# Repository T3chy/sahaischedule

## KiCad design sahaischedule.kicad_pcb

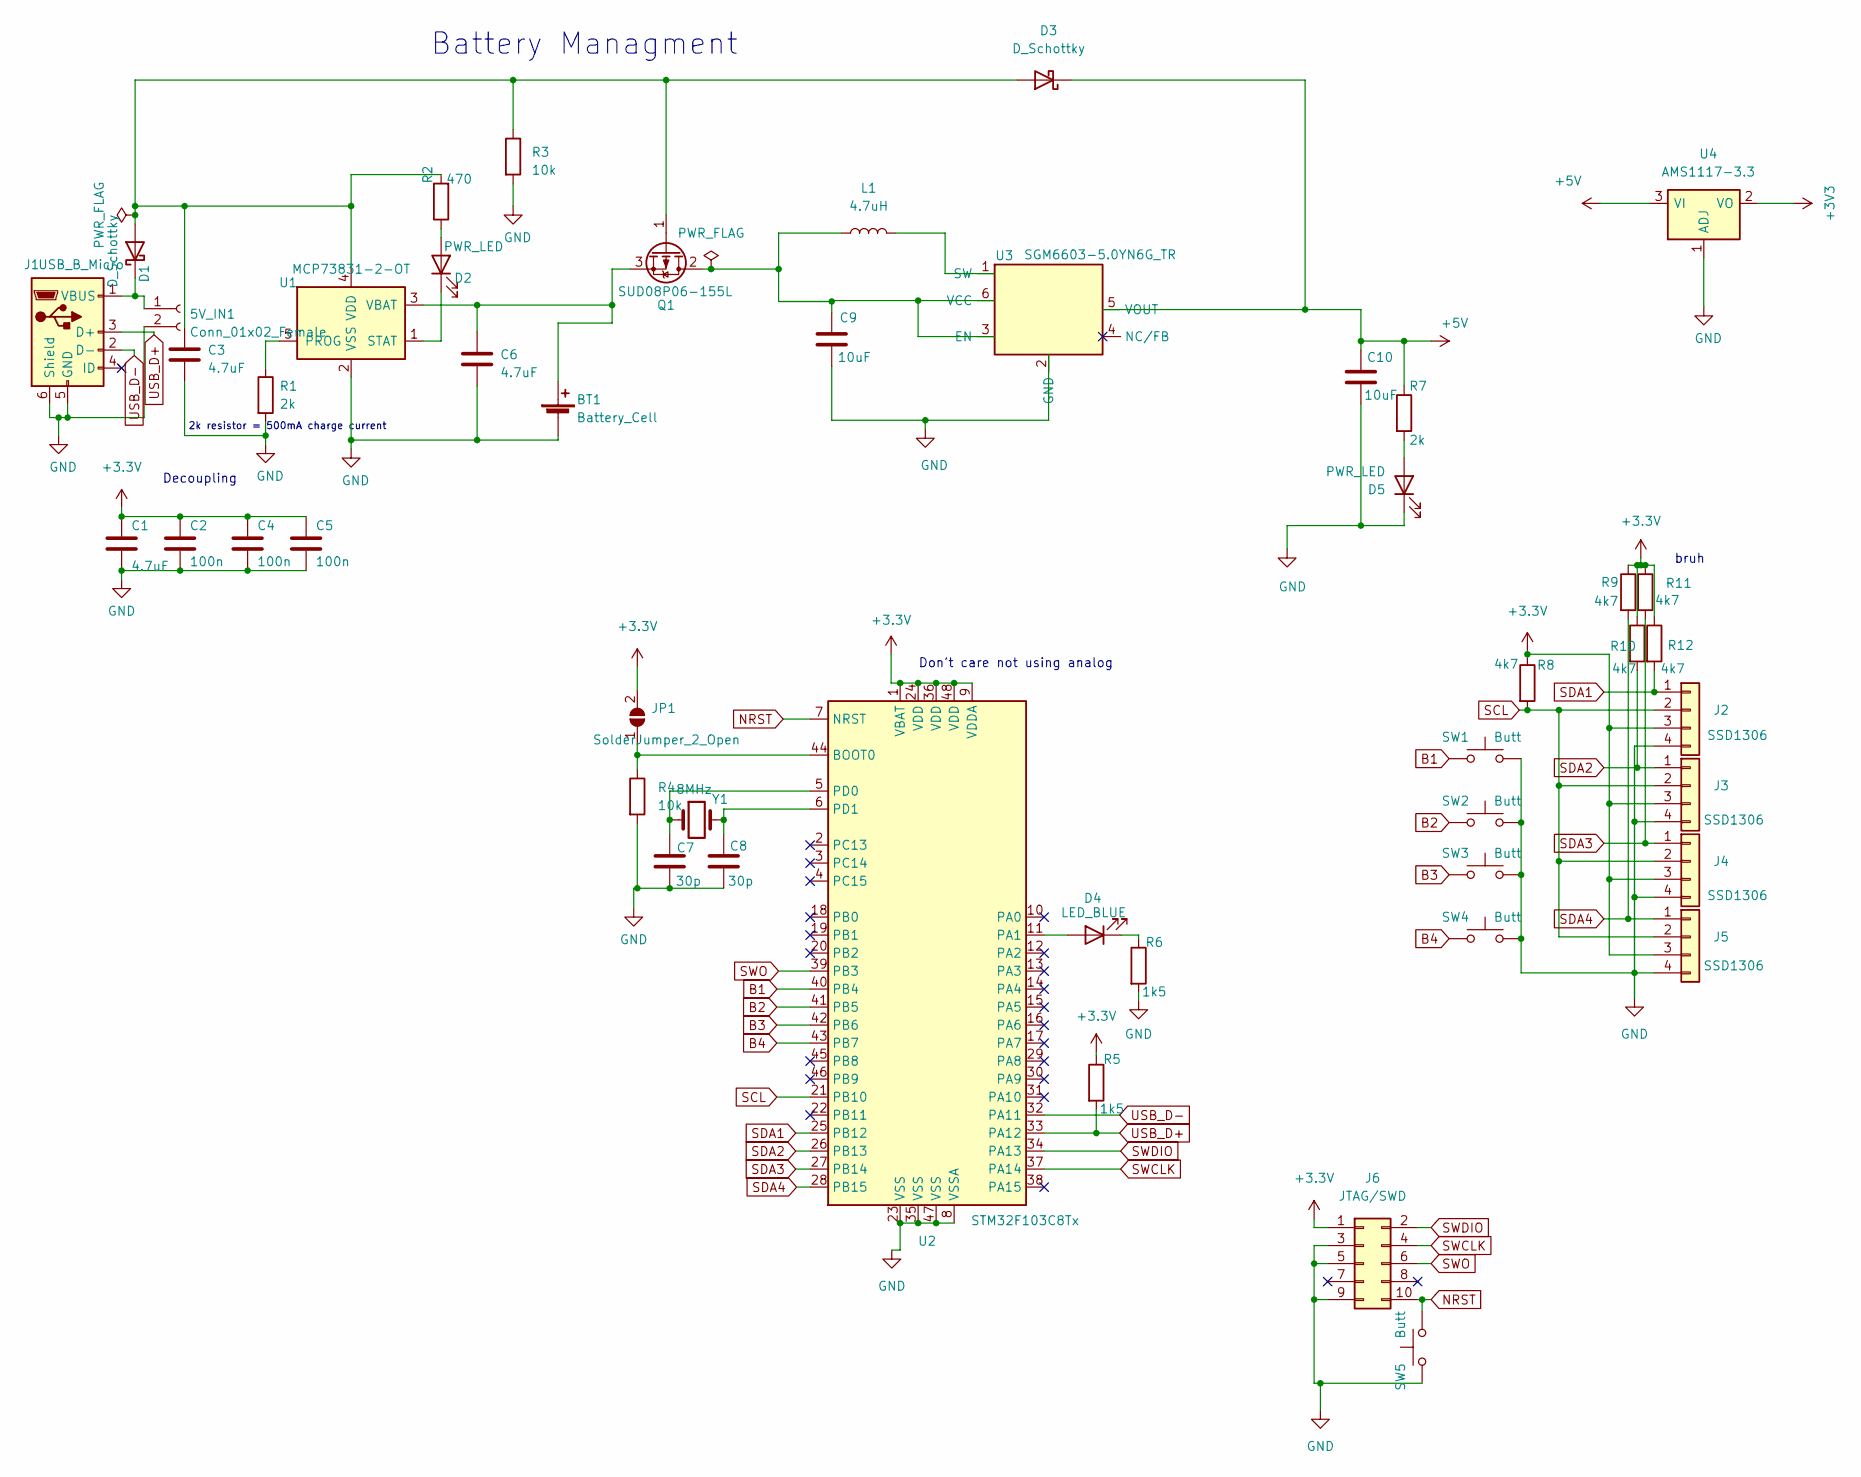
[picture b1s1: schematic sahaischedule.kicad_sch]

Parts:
5V_IN1: Conn_01x02_Female; PinHeader_1x02_P2.54mm_Vertical; mfr_part_num C124375; LCSC C124375
BT1: Battery_Cell; JST_EH_S2B-EH_1x02_P2.50mm_Horizontal; mfr_part_num A2501WR-2P; LCSC C225399
C1, C3, C6: 4.7uF; C_0805_2012Metric_Pad1.18x1.45mm_HandSolder; LCSC C408144
C2, C4, C5: 100n; C_0805_2012Metric_Pad1.18x1.45mm_HandSolder; LCSC C495959
C7, C8: 30p; C_0805_2012Metric_Pad1.18x1.45mm_HandSolder
C9, C10: 10uF; C_0805_2012Metric_Pad1.18x1.45mm_HandSolder
D1, D3: D_Schottky; D_SOD-123; LCSC C8598
D2, D5: PWR_LED; LED_0805_2012Metric; LCSC C72037
D4: LED_BLUE; LED_0805_2012Metric
J1: USB_B_Micro; USB_Micro-B_Molex-105017-0001; mfr_part_num MicroXNJ; LCSC C404969
J2, J3, J4, J5: SSD1306; ssd1306_128x32_breakout
J6: JTAG/SWD; PinHeader_2x05_P1.27mm_Vertical_SMD
JP1: SolderJumper_2_Open; SolderJumper-2_P1.3mm_Open_Pad1.0x1.5mm
L1: 4.7uH; C_0805_2012Metric; LCSC C479902
Q1: SUD08P06-155L; TO-252-2; LCSC C558294
R1, R7: 2k; R_0805_2012Metric_Pad1.20x1.40mm_HandSolder; LCSC C328391
R2: 470; R_0805_2012Metric_Pad1.20x1.40mm_HandSolder; LCSC C136570
R3, R4: 10k; R_0805_2012Metric_Pad1.20x1.40mm_HandSolder
R5, R6: 1k5; R_0805_2012Metric_Pad1.20x1.40mm_HandSolder
R8, R9, R10, R11, R12: 4k7; R_0805_2012Metric_Pad1.20x1.40mm_HandSolder
SW1, SW2, SW3, SW4, SW5: Butt; SW_SPST_Omron_B3FS-101xP; LCSC C589246
U1: MCP73831-2-OT; SOT-23-5; LCSC C424093
U2: STM32F103C8Tx; LQFP-48_7x7mm_P0.5mm; Mouser 497-18592-ND
U3: SGM6603-5.0YN6G_TR; SOT-23-6; LCSC C79689
U4: AMS1117-3.3; SOT-223-3_TabPin2; mfr_part_num AMS1117-3.3; LCSC C369933
Y1: 8MHz; Crystal_SMD_5032-2Pin_5.0x3.2mm_HandSoldering; LCSC C115962

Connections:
+5V: C10.1, D3.1 (K), R7.1, U3.5 (VOUT), U4.3 (VI)
B1: SW1.2, U2.40 (PB4)
B2: SW2.2, U2.41 (PB5)
B3: SW3.2, U2.42 (PB6)
B4: SW4.2, U2.43 (PB7)
GND: 5V_IN1.2, BT1.2 (-), C1.2, C2.2, C3.2, C4.2, C5.2, C6.2, C7.2, C8.2, C9.2, C10.2, D5.1 (K), J1.5 (GND), J1.6 (Shield), J2.4 (GND), J3.4 (GND), J4.4 (GND), J5.4 (GND), J6.3, J6.5, J6.9, R1.2, R3.2, R4.2, R6.2, SW1.1, SW2.1, SW3.1, SW4.1, SW5.2, U1.2 (VSS), U2.8 (VSSA), U2.23 (VSS), U2.35 (VSS), U2.47 (VSS), U3.2 (GND), U4.1 (ADJ)
NRST: J6.10, SW5.1, U2.7 (NRST)
unnamed: 5V_IN1.1, D1.1 (K), J1.1 (VBUS)
unnamed: C3.1, D1.2 (A), D3.2 (A), Q1.1 (G), R2.2, R3.1, U1.4 (VDD)
unnamed: BT1.1 (+), C6.1, Q1.3 (S), U1.3 (VBAT)
unnamed: C7.1, U2.5 (PD0), Y1.1
unnamed: C8.1, U2.6 (PD1), Y1.2
unnamed: C9.1, L1.1, Q1.2 (D), U3.3 (EN), U3.6 (VCC)
unnamed: D2.1 (K), U1.1 (STAT)
unnamed: D2.2 (A), R2.1
unnamed: D4.1 (K), R6.1
unnamed: D4.2 (A), U2.11 (PA1)
unnamed: D5.2 (A), R7.2
unnamed: JP1.1 (A), R4.1, U2.44 (BOOT0)
unnamed: L1.2, U3.1 (SW)
unnamed: R1.1, U1.5 (PROG)
SCL: J2.2 (SCL), J3.2 (SCL), J4.2 (SCL), J5.2 (SCL), R8.2, U2.21 (PB10)
SDA1: J2.1 (SDA), R12.2, U2.25 (PB12)
SDA2: J3.1 (SDA), R10.2, U2.26 (PB13)
SDA3: J4.1 (SDA), R11.2, U2.27 (PB14)
SDA4: J5.1 (SDA), R9.2, U2.28 (PB15)
SWCLK: J6.4, U2.37 (PA14)
SWDIO: J6.2, U2.34 (PA13)
SWO: J6.6, U2.39 (PB3)
USB_D+: J1.3 (D+), R5.2, U2.33 (PA12)
USB_D-: J1.2 (D-), U2.32 (PA11)

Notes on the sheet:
Decoupling
2k resistor = 500mA charge current
Battery Managment
Don't care not using analog
bruh

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
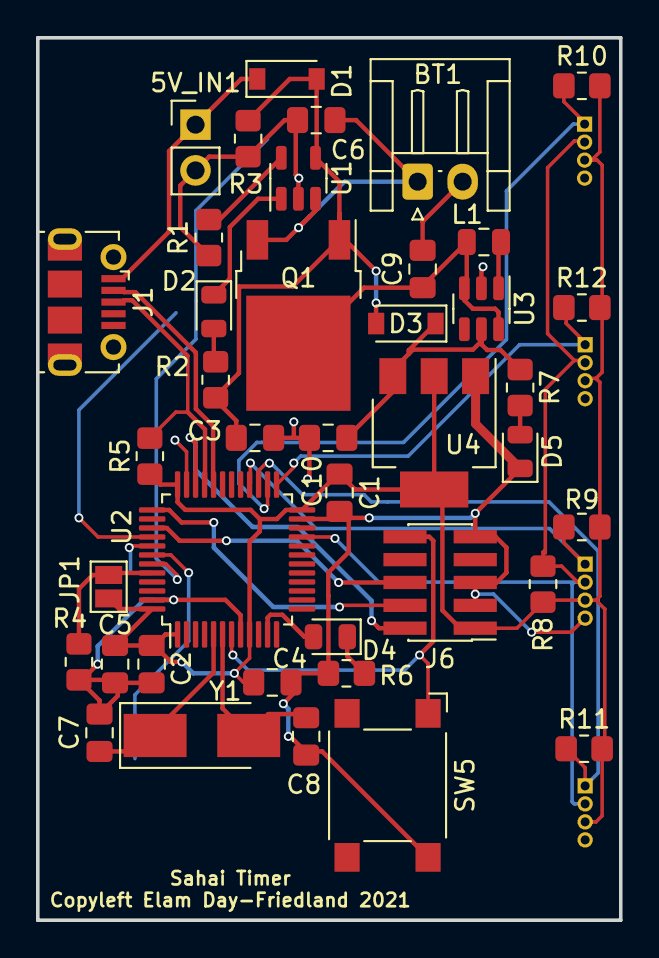
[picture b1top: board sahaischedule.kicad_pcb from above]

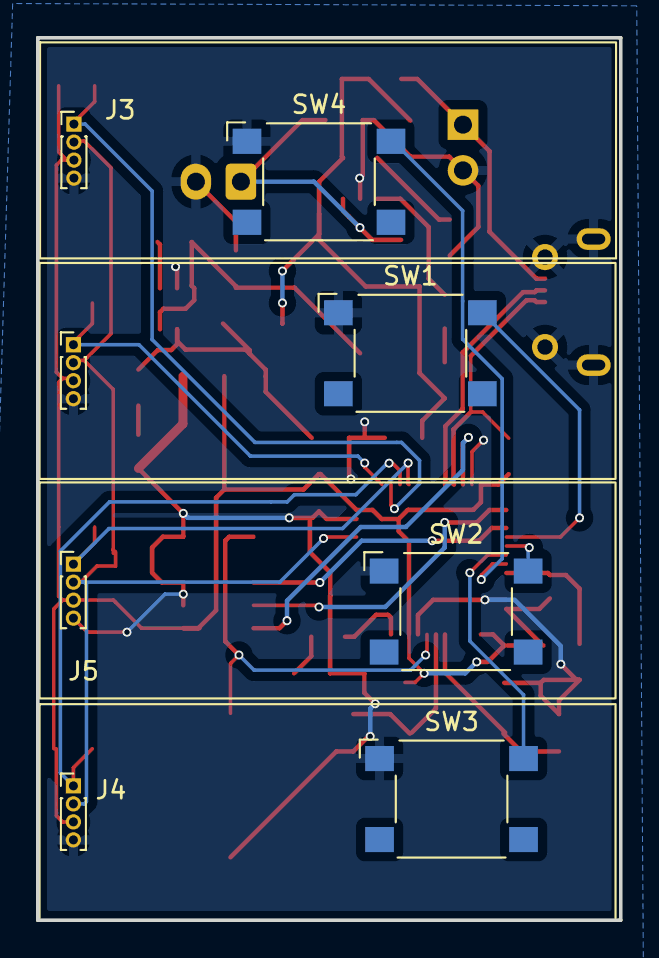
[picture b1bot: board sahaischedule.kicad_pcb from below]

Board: 2 copper layers, 32.4 x 49.0 mm, 48 parts (8 on the bottom side), 32 nets.

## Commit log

2021-09-27 sahai
2021-09-27 more stuff
2021-09-28 added my name

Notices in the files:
sahaischedule.kicad_pcb:
Copyleft Elam Day-Friedland 2021
